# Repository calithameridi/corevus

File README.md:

# corevus

Copyright 2024 by meridi (myself), all rights reserved until I decide on a suitable license

Corevus-G v0.6 printer mainboards are available for evaluation and beta testing. Join the discord: 
`discord (dot) gg (slash) W 5 m a f w 2 k Y h`. **See the [Corevus-G v0.6 manual here](./docs/CvG-v0.6-beta/CvG-v0.6-manual.md)** for more information.

High performance, low-ish price control board for 3D printers. 

(For older hardware releases, also see the [CvG v0.4 manual](./docs/CvG-v0.4-beta/CvG-v0.4-hardware-overview.md))

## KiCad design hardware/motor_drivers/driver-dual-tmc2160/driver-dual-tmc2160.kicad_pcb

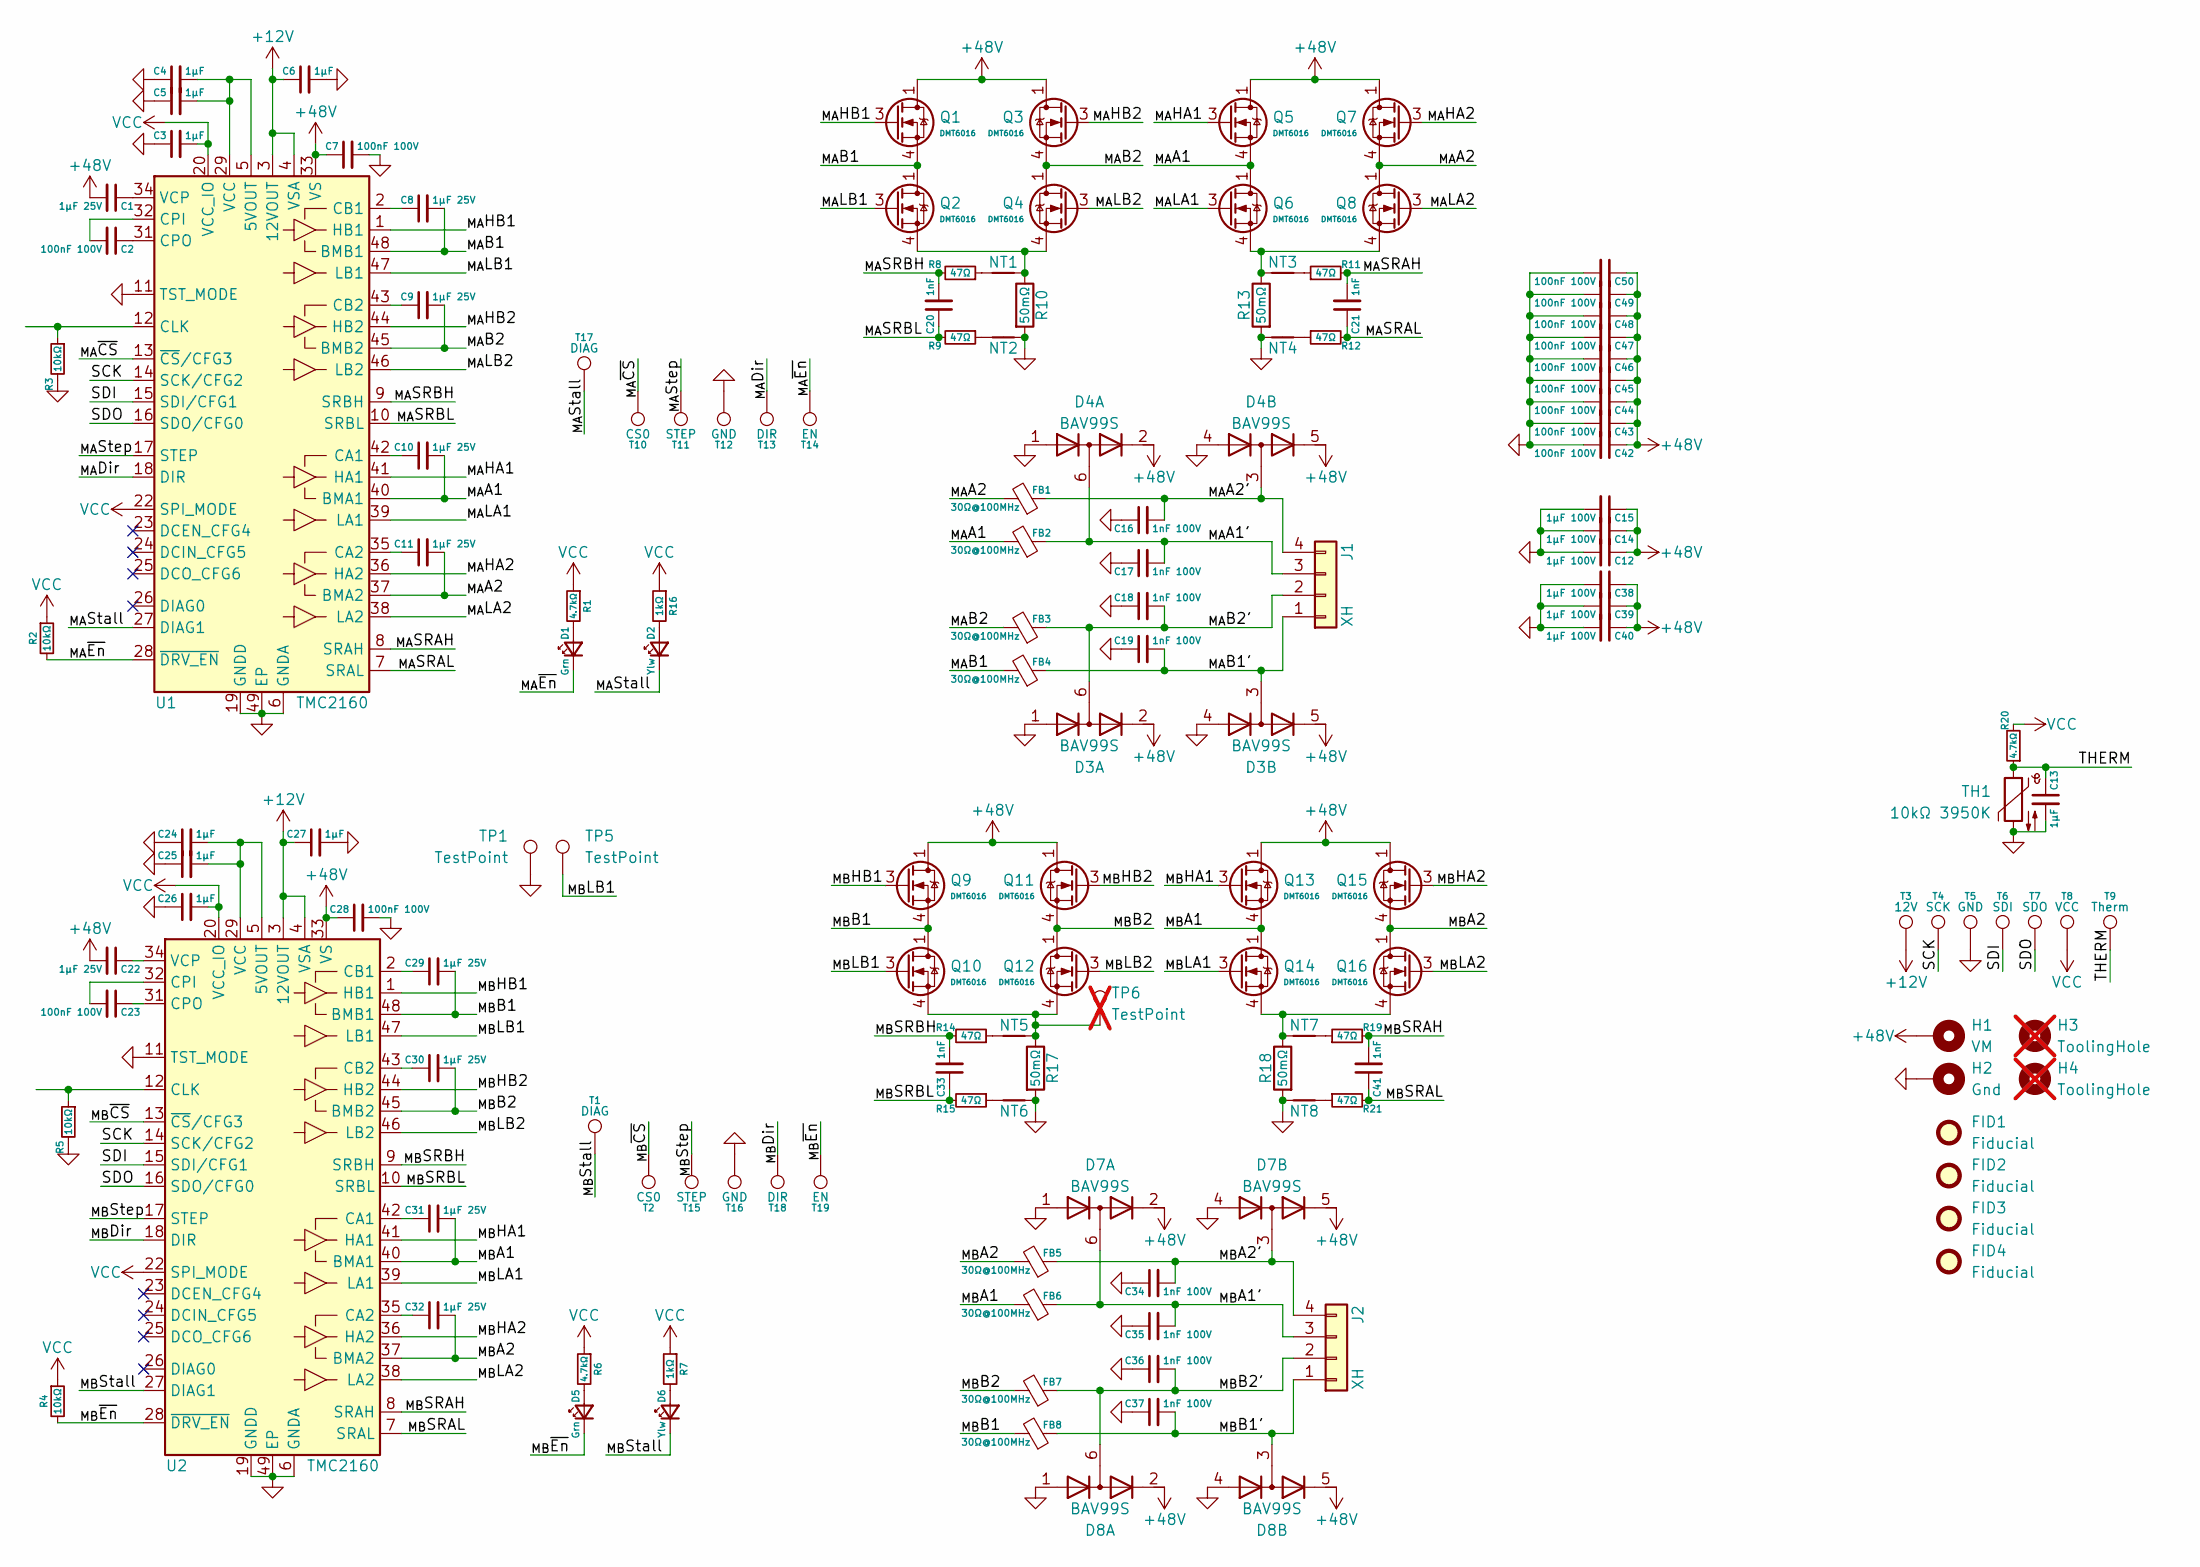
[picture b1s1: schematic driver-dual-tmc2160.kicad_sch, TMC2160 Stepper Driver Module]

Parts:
C1, C8, C9, C10, C11, C22, C29, C30, C31, C32: 1μF 25V; 0402C
C2, C7, C23, C28, C42, C43, C44, C45, C46, C47, C48, C49, C50: 100nF 100V; 0402C
C3, C5, C25, C26: 1µF; 0402C
C4, C6, C13, C24, C27: 1μF; 0402C
C12, C14, C15, C38, C39, C40: 1μF 100V; C_1206_3216Metric
C16, C17, C18, C19, C34, C35, C36, C37: 1nF 100V; 0402C
C20, C21, C33, C41: 1nF; 0402C
D1, D5: Grn; 0603LED
D2, D6: Ylw; 0603LED
D3, D4, D7, D8: BAV99S; SOT-363_SC-70-6
FB1, FB2, FB3, FB4, FB5, FB6, FB7, FB8: 30Ω@100MHz; R_1206_3216Metric
FID1, FID2, FID3, FID4: Fiducial; Fiducial_0.5mm_Mask1mm
H1: VM; MountingHole_M3_Driver
H2: Gnd; MountingHole_M3_Driver
H3, H4: ToolingHole; not fitted
J1, J2: XH; JST_XH_1x04
NT1, NT2, NT3, NT4, NT5, NT6, NT7, NT8: NetTie_2; NetTie-2_SMD_Pad0.15mm
Q1, Q2, Q3, Q4, Q5, Q6, Q7, Q8, Q9, Q10, Q11, Q12, Q13, Q14, Q15, Q16: DMT6016; DMT6016LFDF; LCSC Part C460205
R1, R6, R20: 4.7kΩ; 0402R
R2, R3, R4, R5: 10kΩ; 0402R
R7, R16: 1kΩ; 0402R
R8, R9, R11, R12, R14, R15, R19, R21: 47Ω; 0402R
R10, R13, R17, R18: 50mΩ; R_1206_3216Metric
T1, T17: DIAG; LGA_Land_2.5mm
T2, T10: CS0; LGA_Land_2.5mm
T3: 12V; LGA_Land_2.5mm
T4: SCK; LGA_Land_2.5mm
T5, T12, T16: GND; LGA_Land_2.5mm
T6: SDI; LGA_Land_2.5mm
T7: SDO; LGA_Land_2.5mm
T8: VCC; LGA_Land_2.5mm
T9: Therm; LGA_Land_2.5mm
T11, T15: STEP; LGA_Land_2.5mm
T13, T18: DIR; LGA_Land_2.5mm
T14, T19: EN; LGA_Land_2.5mm
TH1: 10kΩ 3950K; 0402R
TP1, TP5: TestPoint; TestPoint_Pad_D1.0mm
TP6: TestPoint; TestPoint_Pad_D1.0mm; not fitted
U1, U2: TMC2160; TMCx160

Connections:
+12V: C6.1, C27.1, T3.1, U1.3 (12VOUT), U1.4 (VSA), U2.3 (12VOUT), U2.4 (VSA)
+48V: C1.2, C7.1, C12.1, C14.1, C15.1, C22.2, C28.1, C38.1, C39.1, C40.1, C42.1, C43.1, C44.1, C45.1, C46.1, C47.1, C48.1, C49.1, C50.1, D3.2 (K2), D3.5 (K4), D4.2 (K2), D4.5 (K4), D7.2 (K2), D7.5 (K4), D8.2 (K2), D8.5 (K4), H1.1, Q1.1 (D), Q1.2 (D), Q1.5 (D), Q1.6 (D), Q1.8 (D), Q3.1 (D), Q3.2 (D), Q3.5 (D), Q3.6 (D), Q3.8 (D), Q5.1 (D), Q5.2 (D), Q5.5 (D), Q5.6 (D), Q5.8 (D), Q7.1 (D), Q7.2 (D), Q7.5 (D), Q7.6 (D), Q7.8 (D), Q9.1 (D), Q9.2 (D), Q9.5 (D), Q9.6 (D), Q9.8 (D), Q11.1 (D), Q11.2 (D), Q11.5 (D), Q11.6 (D), Q11.8 (D), Q13.1 (D), Q13.2 (D), Q13.5 (D), Q13.6 (D), Q13.8 (D), Q15.1 (D), Q15.2 (D), Q15.5 (D), Q15.6 (D), Q15.8 (D), U1.33 (VS), U2.33 (VS)
/SCK: T4.1, U1.14 (SCK/CFG2), U2.14 (SCK/CFG2)
/SDI: T6.1, U1.15 (SDI/CFG1), U2.15 (SDI/CFG1)
/SDO: T7.1, U1.16 (SDO/CFG0), U2.16 (SDO/CFG0)
/THERM: C13.1, R20.1, T9.1, TH1.1
/_{MA}A1: C10.2, FB2.2, Q5.4 (S), Q5.7 (S), Q6.1 (D), Q6.2 (D), Q6.5 (D), Q6.6 (D), Q6.8 (D), U1.40 (BMA1)
/_{MA}A1': C17.2, D4.6 (K3A4), FB2.1, J1.3
/_{MA}A2: C11.2, FB1.2, Q7.4 (S), Q7.7 (S), Q8.1 (D), Q8.2 (D), Q8.5 (D), Q8.6 (D), Q8.8 (D), U1.37 (BMA2)
/_{MA}A2': C16.2, D4.3 (K1A2), FB1.1, J1.4
/_{MA}B1: C8.2, FB4.2, Q1.4 (S), Q1.7 (S), Q2.1 (D), Q2.2 (D), Q2.5 (D), Q2.6 (D), Q2.8 (D), U1.48 (BMB1)
/_{MA}B1': C19.2, D3.3 (K1A2), FB4.1, J1.1
/_{MA}B2: C9.2, FB3.2, Q3.4 (S), Q3.7 (S), Q4.1 (D), Q4.2 (D), Q4.5 (D), Q4.6 (D), Q4.8 (D), U1.45 (BMB2)
/_{MA}B2': C18.2, D3.6 (K3A4), FB3.1, J1.2
/_{MA}Dir: T13.1, U1.18 (DIR)
/_{MA}HA1: Q5.3 (G), U1.41 (HA1)
/_{MA}HA2: Q7.3 (G), U1.36 (HA2)
/_{MA}HB1: Q1.3 (G), U1.1 (HB1)
/_{MA}HB2: Q3.3 (G), U1.44 (HB2)
/_{MA}LA1: Q6.3 (G), U1.39 (LA1)
/_{MA}LA2: Q8.3 (G), U1.38 (LA2)
/_{MA}LB1: Q2.3 (G), U1.47 (LB1)
/_{MA}LB2: Q4.3 (G), U1.46 (LB2)
/_{MA}SRAH: C21.2, R11.2, U1.8 (SRAH)
/_{MA}SRAL: C21.1, R12.2, U1.7 (SRAL)
/_{MA}SRBH: C20.2, R8.2, U1.9 (SRBH)
/_{MA}SRBL: C20.1, R9.2, U1.10 (SRBL)
/_{MA}Stall: D2.1 (K), T17.1, U1.27 (DIAG1)
/_{MA}Step: T11.1, U1.17 (STEP)
/_{MA}~CS: T10.1, U1.13 (~CS/CFG3)
/_{MA}~En: D1.1 (K), R2.2, T14.1, U1.28 (~DRV_EN)
/_{MB}A1: C31.2, FB6.2, Q13.4 (S), Q13.7 (S), Q14.1 (D), Q14.2 (D), Q14.5 (D), Q14.6 (D), Q14.8 (D), U2.40 (BMA1)
/_{MB}A1': C35.2, D7.6 (K3A4), FB6.1, J2.3
/_{MB}A2: C32.2, FB5.2, Q15.4 (S), Q15.7 (S), Q16.1 (D), Q16.2 (D), Q16.5 (D), Q16.6 (D), Q16.8 (D), U2.37 (BMA2)
/_{MB}A2': C34.2, D7.3 (K1A2), FB5.1, J2.4
/_{MB}B1: C29.2, FB8.2, Q9.4 (S), Q9.7 (S), Q10.1 (D), Q10.2 (D), Q10.5 (D), Q10.6 (D), Q10.8 (D), U2.48 (BMB1)
/_{MB}B1': C37.2, D8.3 (K1A2), FB8.1, J2.1
/_{MB}B2: C30.2, FB7.2, Q11.4 (S), Q11.7 (S), Q12.1 (D), Q12.2 (D), Q12.5 (D), Q12.6 (D), Q12.8 (D), U2.45 (BMB2)
/_{MB}B2': C36.2, D8.6 (K3A4), FB7.1, J2.2
/_{MB}Dir: T18.1, U2.18 (DIR)
/_{MB}HA1: Q13.3 (G), U2.41 (HA1)
/_{MB}HA2: Q15.3 (G), U2.36 (HA2)
/_{MB}HB1: Q9.3 (G), U2.1 (HB1)
/_{MB}HB2: Q11.3 (G), U2.44 (HB2)
/_{MB}LA1: Q14.3 (G), U2.39 (LA1)
/_{MB}LA2: Q16.3 (G), U2.38 (LA2)
/_{MB}LB1: Q10.3 (G), TP5.1, U2.47 (LB1)
/_{MB}LB2: Q12.3 (G), U2.46 (LB2)
/_{MB}SRAH: C41.2, R19.2, U2.8 (SRAH)
/_{MB}SRAL: C41.1, R21.2, U2.7 (SRAL)
/_{MB}SRBH: C33.2, R14.2, U2.9 (SRBH)
/_{MB}SRBL: C33.1, R15.2, U2.10 (SRBL)
/_{MB}Stall: D6.1 (K), T1.1, U2.27 (DIAG1)
/_{MB}Step: T15.1, U2.17 (STEP)
/_{MB}~CS: T2.1, U2.13 (~CS/CFG3)
/_{MB}~En: D5.1 (K), R4.2, T19.1, U2.28 (~DRV_EN)
GND: C3.1, C4.1, C5.1, C6.2, C7.2, C12.2, C13.2, C14.2, C15.2, C16.1, C17.1, C18.1, C19.1, C24.1, C25.1, C26.1, C27.2, C28.2, C34.1, C35.1, C36.1, C37.1, C38.2, C39.2, C40.2, C42.2, C43.2, C44.2, C45.2, C46.2, C47.2, C48.2, C49.2, C50.2, D3.1 (A1), D3.4 (A3), D4.1 (A1), D4.4 (A3), D7.1 (A1), D7.4 (A3), D8.1 (A1), D8.4 (A3), H2.1, NT2.2, NT4.1, NT6.2, NT8.1, R3.2, R5.2, R10.2, R13.2, R17.2, R18.2, T5.1, T12.1, T16.1, TH1.2, TP1.1, U1.6 (GNDA), U1.11 (TST_MODE), U1.19 (GNDD), U1.30 (GNDD), U1.49 (EP), U2.6 (GNDA), U2.11 (TST_MODE), U2.19 (GNDD), U2.30 (GNDD), U2.49 (EP)
unnamed: D1.2 (A), R1.2
unnamed: D2.2 (A), R16.2
unnamed: D5.2 (A), R6.2
unnamed: D6.2 (A), R7.2
unnamed: NT1.1, R8.1
unnamed: NT1.2, Q2.4 (S), Q2.7 (S), Q4.4 (S), Q4.7 (S), R10.1
unnamed: NT2.1, R9.1
unnamed: NT3.1, Q6.4 (S), Q6.7 (S), Q8.4 (S), Q8.7 (S), R13.1
unnamed: NT3.2, R11.1
unnamed: NT4.2, R12.1
unnamed: NT5.1, R14.1
unnamed: NT5.2, Q10.4 (S), Q10.7 (S), Q12.4 (S), Q12.7 (S), R17.1, TP6.1
unnamed: NT6.1, R15.1
unnamed: NT7.1, Q14.4 (S), Q14.7 (S), Q16.4 (S), Q16.7 (S), R18.1
unnamed: NT7.2, R19.1
unnamed: NT8.2, R21.1
unnamed: C4.2, C5.2, U1.5 (5VOUT), U1.29 (VCC)
unnamed: C10.1, U1.42 (CA1)
unnamed: C11.1, U1.35 (CA2)
unnamed: C8.1, U1.2 (CB1)
unnamed: C9.1, U1.43 (CB2)
unnamed: R3.1, U1.12 (CLK)
unnamed: C2.2, U1.32 (CPI)
unnamed: C2.1, U1.31 (CPO)
unnamed: C1.1, U1.34 (VCP)
unnamed: C24.2, C25.2, U2.5 (5VOUT), U2.29 (VCC)
unnamed: C31.1, U2.42 (CA1)
unnamed: C32.1, U2.35 (CA2)
unnamed: C29.1, U2.2 (CB1)
unnamed: C30.1, U2.43 (CB2)
unnamed: R5.1, U2.12 (CLK)
unnamed: C23.2, U2.32 (CPI)
unnamed: C23.1, U2.31 (CPO)
unnamed: C22.1, U2.34 (VCP)
VCC: C3.2, C26.2, R1.1, R2.1, R4.1, R6.1, R7.1, R16.1, R20.2, T8.1, U1.20 (VCC_IO), U1.21 (VCC_IO), U1.22 (SPI_MODE), U2.20 (VCC_IO), U2.21 (VCC_IO), U2.22 (SPI_MODE)

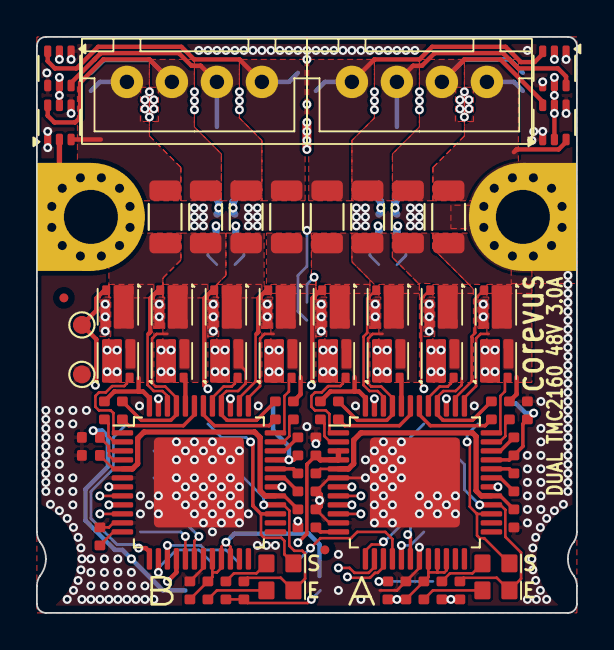
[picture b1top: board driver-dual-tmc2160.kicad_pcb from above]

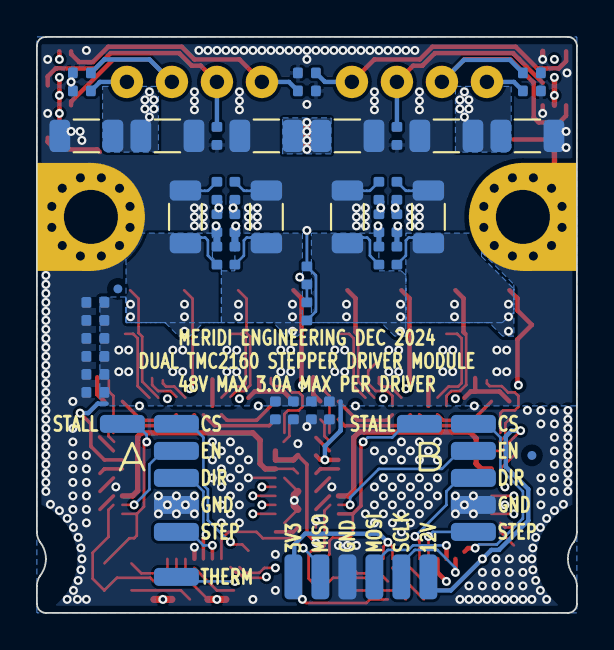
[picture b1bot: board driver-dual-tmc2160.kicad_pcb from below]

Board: 4 copper layers, 30.0 x 32.0 mm, 143 parts (71 on the bottom side), 92 nets.

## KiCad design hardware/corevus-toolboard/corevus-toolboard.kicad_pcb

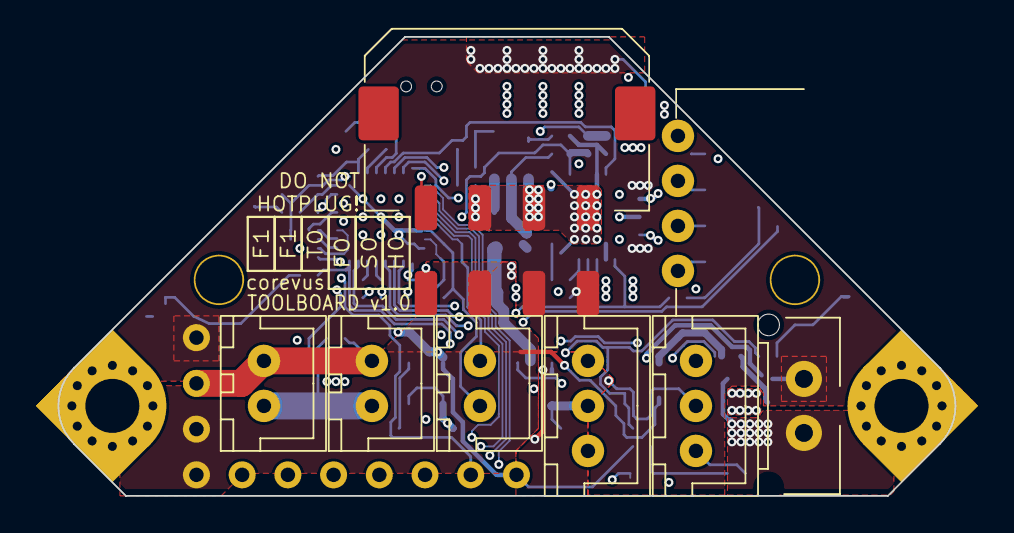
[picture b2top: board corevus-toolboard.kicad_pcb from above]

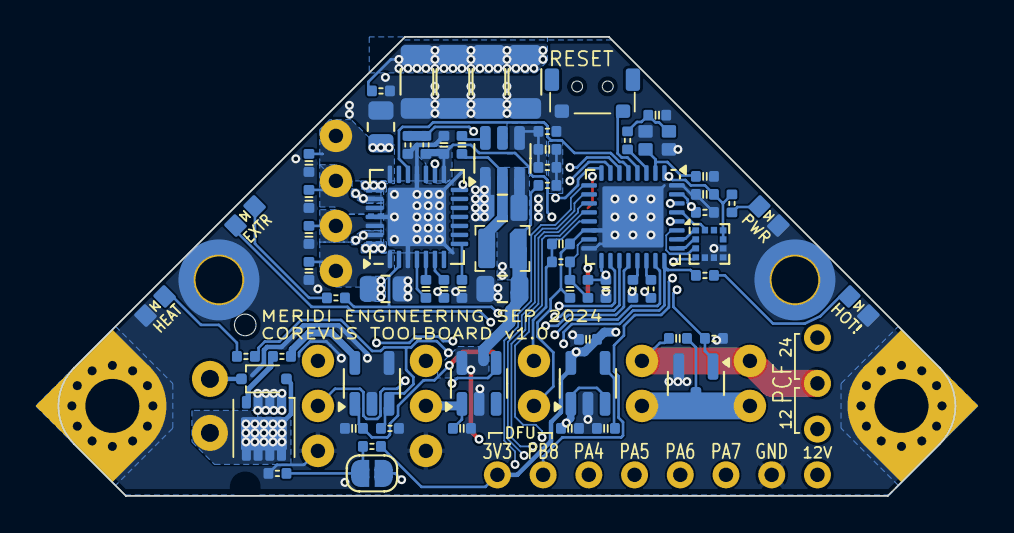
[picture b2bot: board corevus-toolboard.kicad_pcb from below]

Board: 4 copper layers, 49.8 x 25.5 mm, 84 parts (72 on the bottom side), 62 nets.

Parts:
C1, C4, C5, C6, C11, C12, C13, C26, C34: 1µF; 0402C
C2, C3: 10pF; 0402C
C7: 100nF; 0402C
C8: 100nF 16V; 0402C
C9: 22nF 50V; 0402C
C14, C15, C16, C17: 10µF 50V; C_1206_3216Metric
C18, C19, C20, C21: 470pF; 0402C
C23: 100nF 50V; 0402C
C28: 68pF; 0402C
C29: 100nF 25V; 0402C
C31: 10nF; 0402C
C32: 10µF 25V; C_0805_2012Metric
C33: 10µF; C_0805_2012Metric
D1: 4148; D_SOD-323
D2: Red; 0603LED
D3: Grn; 0603LED
D4: Wht; 0603LED
D5: Ylw; 0603LED
FB1: GZ1005; 0402
H1, H2: M3 Hole; MountingHole_M3_Driver_Corner
H3, H4: M2 Standoff; Sinhoo_TH162010
J1: MF3 1x2P; Molex_Micro-Fit-3.0_436500215
J2, J9: XH 1x3P; JST_XH_1x03
J3: MX3.0 2x4P; XKB_X3025WRS-2x04E
J4: XH 1x4P; JST_XH_1x04-Side
J5, J6, J7: XH 1x2P; JST_XH_1x02
J8: 1x8P; PinHeader_1x08_P2.54mm_Vertical
J10: 1x3P; PinHeader_1x03_P2.54mm_Vertical
JP1: Jumper_2_Small_Open; SolderJumper-2_P1.3mm_Open_RoundedPad1.0x1.5mm
L1: 10µH; L_Changjiang_FTC2520
NT1: NetTie_2; NetTie-2_SMD_Pad0.1mm
Q2: NMOS; MOSFET_DFN8
Q4: AO3400; SOT-23
R1, R7, R16: 4.7kΩ; 0402R
R2: 100kΩ; 0402R
R3, R4: 33Ω; 0402R
R5, R6: 100mΩ; R_0805_2012Metric
R8, R13, R17, R21: 2.2kΩ; 0402R
R9: 0Ω; 0402R
R10: 20kΩ; 0402R
R11: 150kΩ; 0402R
R12: 1kΩ; 0402R
R14, R19: 10kΩ; 0402R
R15: 51Ω; 0402R
R20: 510kΩ; 0402R
SW1: Reset; ShouHan_TS24CA
TH1, TH2: 10kΩ 3950K; 0402R
U1: LIS2DE12; LGA-12_2x2mm_P0.5mm
U2: TPS54302; SOT-23-6
U3: STM32G431KBU3; QFN-32-1EP_5x5mm_P0.5mm_EP3.45x3.45mm
U4: TMC2209-LA; TQFN-28-1EP_5x5mm_P0.5mm_EP3.25x3.25mm_ThermalVias
U6: SPX3819M5-L-3-3; SOT-23-5
U7: TPS2069CDBV; SOT-23-5
U8: UCC27517; SOT-23-5
Y1: XRCGB25; Crystal_SMD_2016-4Pin_2.0x1.6mm

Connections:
+3.3V: C5.1, C11.1, C12.1, C34.2, D3.2 (A), FB1.2, J8.8, R7.2, R16.2, R17.2, U1.9 (Vdd), U1.10 (Vdd_IO), U3.1 (VDD), U3.17 (VDD), U4.15 (VCC_IO), U6.5 (OUT)
+5V: C1.2, C33.1, J9.2, L1.2, R15.1, U6.1 (IN), U6.3 (EN), U7.5 (IN)
+12V: C29.1, C32.1, J3.6, J8.1, J10.3, U2.3 (VIN), U8.1 (VDD)
+24V: C8.2, C14.1, C15.1, C16.1, C17.1, D1.1 (K), J1.2, J3.7, J3.8, J10.1, R20.1, U4.22 (VS), U4.28 (VS)
/A1: C19.1, J4.3, U4.24 (OA1)
/A2: C18.1, J4.4, U4.21 (OA2)
/ACCEL_CS: U1.2 (~CS), U3.25 (PA15)
/ACCEL_INT1: U1.12 (INT1), U3.29 (PB6)
/B1: C21.1, J4.1, U4.1 (OB2)
/B2: C20.1, J4.2, U4.26 (OB1)
/BOOT0: J8.7, R2.2, U3.31 (PB8)
/D+: J3.5, R3.2
/D+': R3.1, U3.22 (USB_DP)
/D-: J3.1, R4.2
/D-': R4.1, U3.21 (USB_DM)
/Dir: U3.5 (PA0), U4.19 (DIR)
/F0: R8.2, U3.24 (PA14), U7.4 (EN)
/F0_FG: J2.3, U3.19 (PA9)
/F1: Q4.1 (G), R14.1, U3.30 (PB7)
/H0: R1.2, R19.2, U3.23 (PA13), U8.3 (IN+)
/H0_Gate: R9.2, U8.5 (OUT)
/PA4: J8.6, JP1.2 (B), U3.9 (ADC2_IN17)
/PA5: J8.5, U3.10 (ADC2_IN13)
/PA6: J8.4, U3.11 (ADC2_IN3)
/PA7: J8.3, U3.12 (ADC2_IN4)
/PCF_V+: C23.1, J6.2, J7.2, J10.2
/S0: J9.3, U3.20 (PA10)
/SPI1_MISO: U1.3 (SA0/SDO), U3.27 (SPI1_MISO)
/SPI1_MOSI: U1.4 (SDA/SDI), U3.28 (SPI1_MOSI)
/SPI1_SCK: U1.1 (SCL/SPC), U3.26 (SPI1_SCK)
/Step: U3.7 (PA2), U4.16 (STEP)
/T0: C26.1, J5.2, R13.1, U3.13 (PB0)
/UART: U3.8 (PA3), U4.14 (PDN/UART)
/_{FET}Therm: JP1.1 (A), R7.1, TH2.1
/_{Motor}Therm: R16.1, TH1.1, U3.6 (ADC1_IN2)
/~En: R21.2, U3.18 (PA8), U4.2 (~EN)
/~Reset: SW1.1, U3.4 (PG10)
GND: C1.1, C2.2, C3.2, C4.2, C5.2, C6.2, C11.2, C12.2, C14.2, C15.2, C16.2, C17.2, C18.2, C19.2, C20.2, C21.2, C29.2, C31.1, C32.2, C33.2, C34.1, D2.1 (K), D4.1 (K), D5.1 (K), H1.1, H2.1, H3.1, H4.1, J2.1, J3.2, J3.3, J3.4, J8.2, J9.1, NT1.1, Q2.1 (S), Q2.2 (S), Q2.3 (S), Q4.2 (S), R2.1, R5.1, R6.1, R10.2, R14.2, R19.1, R20.2, SW1.2, TH1.2, TH2.2, U1.5 (RES), U1.6 (GND), U1.7 (GND), U1.8 (GND), U2.1 (GND), U3.16 (VSS), U3.32 (VSS), U3.33 (VSS), U4.3 (GND), U4.18 (Gnd), U4.25 (NC), U4.29 (Pad), U6.2 (GND), U7.2 (GND), U8.2 (GND), U8.4 (IN-), Y1.2, Y1.4
unnamed: C3.1, R12.1, Y1.1
unnamed: C28.1, R11.1, R15.2
unnamed: D1.2 (A), J1.1, Q2.5 (D), Q2.6 (D), Q2.7 (D), Q2.8 (D)
unnamed: D2.2 (A), R1.1
unnamed: D3.1 (K), R21.1
unnamed: D4.2 (A), R17.1
unnamed: D5.2 (A), R8.1
unnamed: C6.1, J2.2, U7.1 (OUT)
unnamed: C23.2, J6.1, J7.1, Q4.3 (D)
unnamed: Q2.4 (G), R9.1
unnamed: C7.1, U2.6 (BOOT)
unnamed: C28.2, R10.1, R11.2, U2.4 (FB)
unnamed: C7.2, L1.1, U2.2 (SW)
unnamed: C2.1, U3.2 (RCC_OSC_IN), Y1.3
unnamed: R12.2, U3.3 (RCC_OSC_OUT)
unnamed: C4.1, U4.8 (5VOUT)
unnamed: R5.2, U4.23 (BRA)
unnamed: R6.2, U4.27 (BRB)
unnamed: C9.2, U4.5 (CPI)
unnamed: C9.1, U4.4 (CPO)
unnamed: C8.1, U4.6 (VCP)
unnamed: C31.2, U6.4 (BP)
VDDA: C13.2, FB1.1, R13.2, U3.15 (VDDA)
VSSA: C13.1, C26.2, J5.1, NT1.2, U3.14 (VSSA)

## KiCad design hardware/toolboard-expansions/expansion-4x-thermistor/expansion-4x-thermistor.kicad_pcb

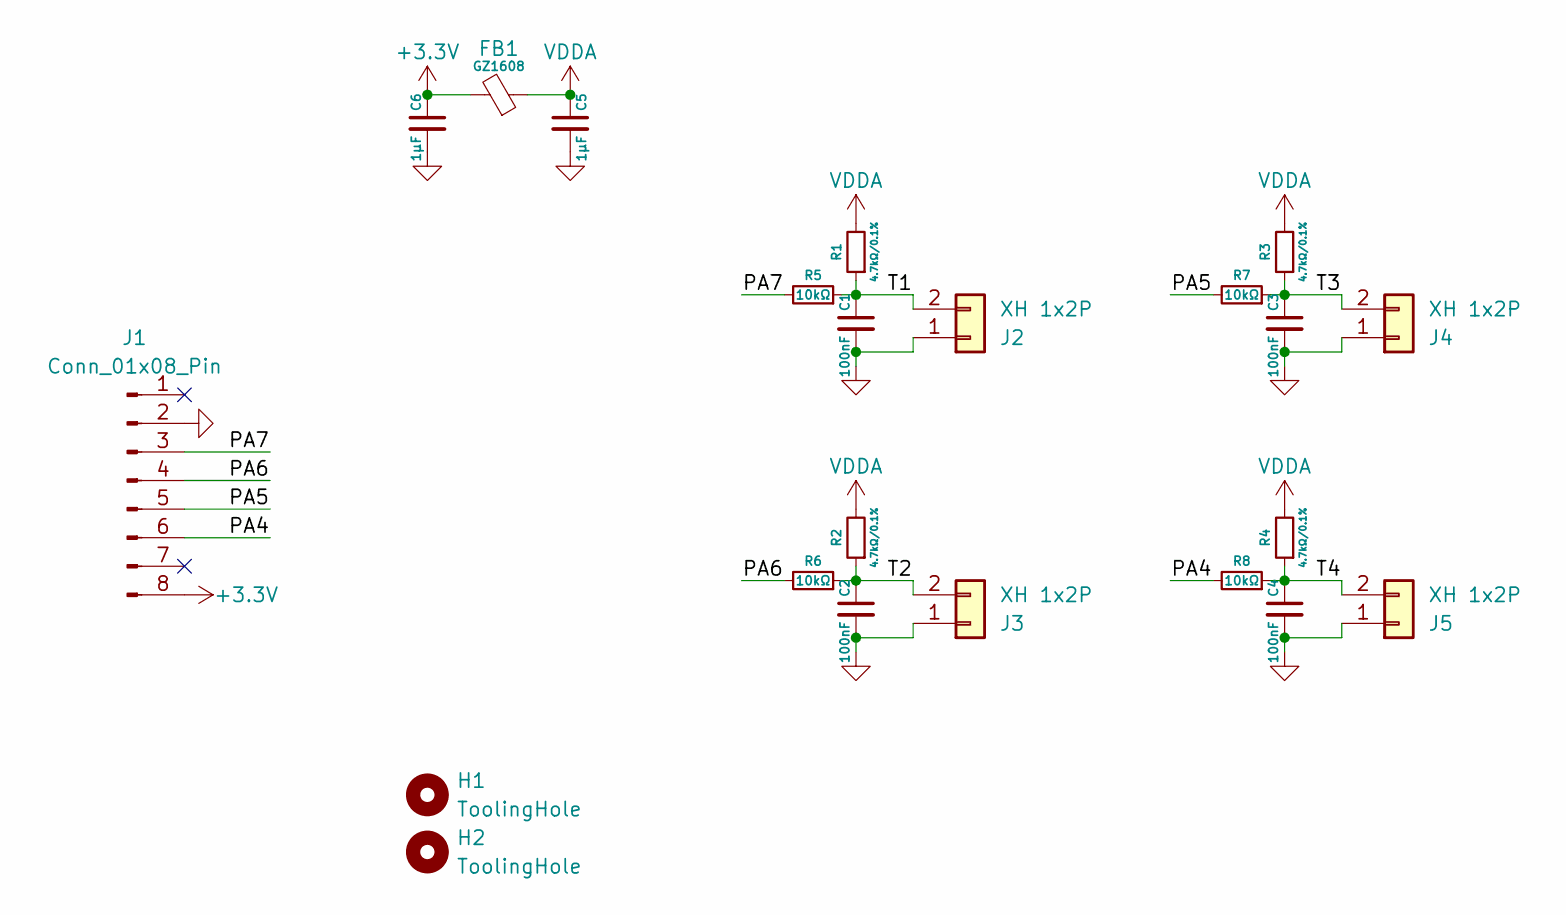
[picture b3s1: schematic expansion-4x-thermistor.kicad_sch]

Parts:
C1, C2, C3, C4: 100nF; 0402C
C5, C6: 1µF; 0402C
FB1: GZ1608; 0603
H1, H2: ToolingHole
J1: Conn_01x08_Pin; PinHeader_1x08_P2.54mm_Vertical
J2, J3, J4, J5: XH 1x2P; JST_XH_1x02-Side
R1, R2, R3, R4: 4.7kΩ/0.1%; 0402R
R5, R6, R7, R8: 10kΩ; 0402R

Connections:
+3.3V: C6.1, FB1.2, J1.8
/PA4: J1.6, R8.2
/PA5: J1.5, R7.2
/PA6: J1.4, R6.2
/PA7: J1.3, R5.2
/T1: C1.1, J2.2, R1.1, R5.1
/T2: C2.1, J3.2, R2.1, R6.1
/T3: C3.1, J4.2, R3.1, R7.1
/T4: C4.1, J5.2, R4.1, R8.1
GND: C1.2, C2.2, C3.2, C4.2, C5.2, C6.2, J1.2, J2.1, J3.1, J4.1, J5.1
VDDA: C5.1, FB1.1, R1.2, R2.2, R3.2, R4.2

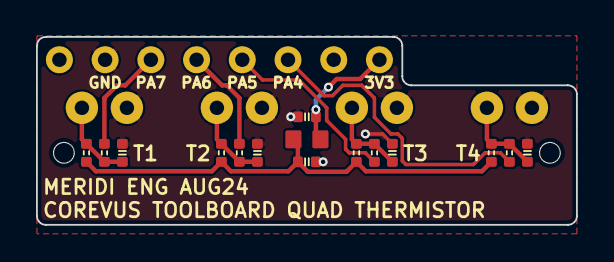
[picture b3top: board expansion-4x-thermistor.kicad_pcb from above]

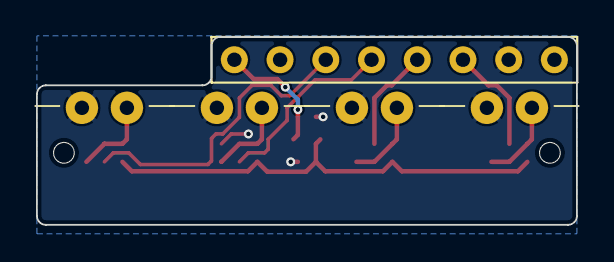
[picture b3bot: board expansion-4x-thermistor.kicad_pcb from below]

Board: 2 copper layers, 30.0 x 10.4 mm, 22 parts (5 on the bottom side), 11 nets.

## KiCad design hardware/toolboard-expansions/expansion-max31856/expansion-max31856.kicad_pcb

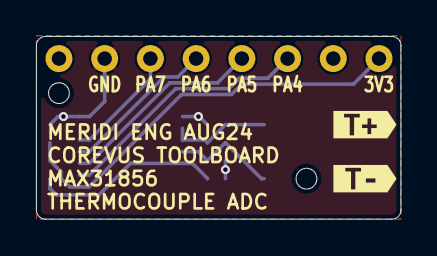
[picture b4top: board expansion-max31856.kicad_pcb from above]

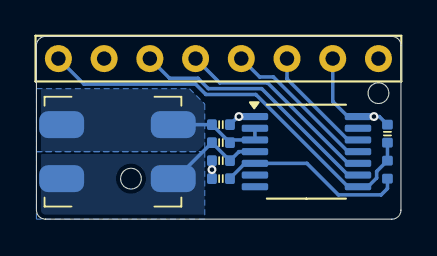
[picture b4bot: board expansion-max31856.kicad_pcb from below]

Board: 2 copper layers, 20.2 x 10.2 mm, 13 parts (9 on the bottom side), 9 nets.

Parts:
C1, C2, C5: 100nF; 0402C
C3, C4: 10nF; 0402C
H1, H2: ToolingHole
J1: Conn_01x08_Socket; PinHeader_1x08_P2.54mm_Vertical
J2: WAGO 1x2P; WAGO_2059-302
R1: 0Ω; 0402
U1: MAX31856; TSSOP-14_4.4x5mm_P0.65mm
kibuzzard-66C1A6C4: G***; kibuzzard-66C1A6C4
kibuzzard-66C1A6D0: G***; kibuzzard-66C1A6D0

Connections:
+3.3V: C1.1, J1.8, R1.1, U1.8 (DVDD)
/PA4: J1.6, U1.9 (~CS)
/PA5: J1.5, U1.10 (SCK)
/PA6: J1.4, U1.11 (SDO)
/PA7: J1.3, U1.12 (SDI)
/T+: C3.2, C5.1, J2.2, U1.4 (T+)
/T-: C4.2, C5.2, J2.1, U1.2 (BIAS), U1.3 (T-)
GND: C1.2, C2.2, C3.1, C4.1, J1.2, U1.1 (AGND), U1.14 (DGND)
VDDA: C2.1, R1.2, U1.5 (AVDD)

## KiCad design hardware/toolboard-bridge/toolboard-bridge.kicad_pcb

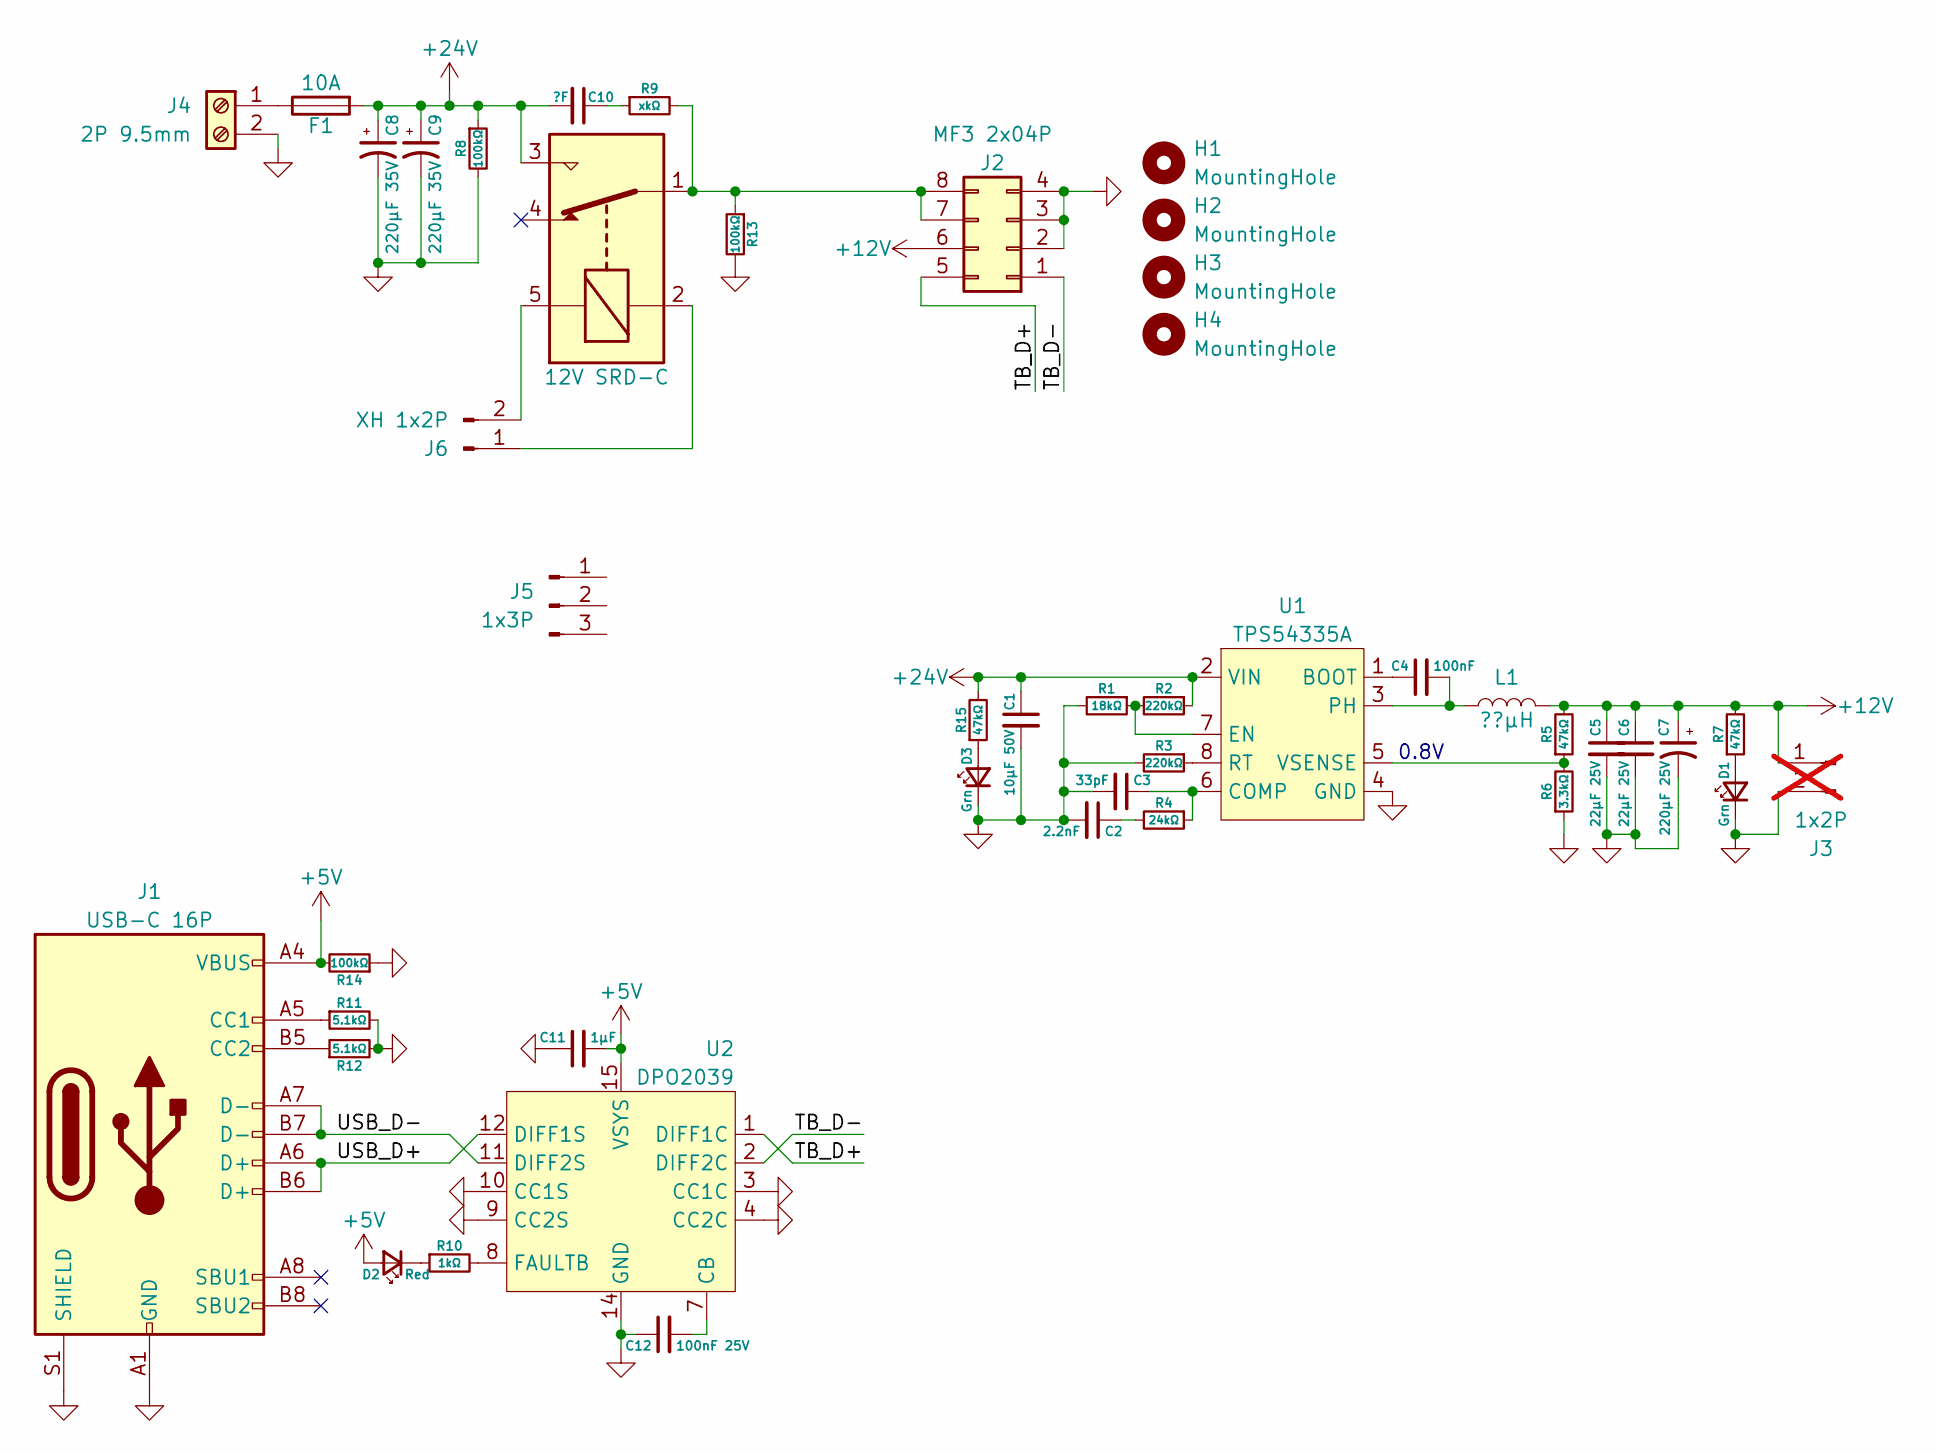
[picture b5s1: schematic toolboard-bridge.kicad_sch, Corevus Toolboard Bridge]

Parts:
C1: 10μF 50V; C_1206_3216Metric
C2: 2.2nF; 0402C
C3: 33pF; 0402C
C4: 100nF; 0402C
C5, C6: 22μF 25V; C_1206_3216Metric
C7: 220μF 25V; CP_Radial_D8.0mm_P3.50mm
C8, C9: 220μF 35V; CP_Radial_D8.0mm_P3.50mm
C10: ?F; C_1206_3216Metric
C11: 1μF; 0402C
C12: 100nF 25V; 0402C
D1, D3: Grn; 0603LED
D2: Red; 0603LED
F1: 10A; XF-506P
H1, H2, H3, H4: MountingHole; MountingHole_3.2mm_M3_DIN965
J1: USB-C 16P; USB_Type-C_16p
J2: MF3 2x04P; Molex_Micro-Fit-3.0_430450813
J3: 1x2P; PinHeader_1x02_P2.54mm_Vertical; not fitted
J4: 2P 9.5mm; Kefa_KF8500-8.5-2P
J5: 1x3P; PinHeader_1x03_P2.54mm_Vertical
J6: XH 1x2P; JST_XH_1x02
K1: 12V SRD-C; Relay_SPDT_SANYOU_SRD_Series_Form_C
L1: ??μH; L_Changjiang_FXL0640
R1: 18kΩ; 0402R
R2, R3: 220kΩ; 0402R
R4: 24kΩ; 0402R
R5: 47kΩ; 0603R
R6: 3.3kΩ; 0603R
R7, R15: 47kΩ; 0402R
R8, R13, R14: 100kΩ; 0402R
R9: xkΩ; 0402R
R10: 1kΩ; 0402R
R11, R12: 5.1kΩ; 0402R
U1: TPS54335A; SOIC-8-1EP_3.9x4.9mm_P1.27mm_EP2.95x4.9mm_Mask2.71x3.4mm_Th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
U2: DPO2039; VQFN-16-1EP_3x3mm_P0.5mm_EP1.6x1.6mm

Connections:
+5V: C11.2, D2.2 (A), J1.A4 (VBUS), J1.A9 (VBUS), J1.B4 (VBUS), J1.B9 (VBUS), R14.2, U2.15 (VSYS)
+12V: C5.1, C6.1, C7.1, J2.6, J3.1, L1.2, R5.2, R7.2
+24V: C1.1, C8.1, C9.1, C10.2, F1.2, K1.3, R2.1, R8.1, R15.2, U1.2 (VIN)
/TB_D+: J2.5, U2.1 (DIFF1C)
/TB_D-: J2.1, U2.2 (DIFF2C)
/USB_D+: J1.A6 (D+), J1.B6 (D+), U2.12 (DIFF1S)
/USB_D-: J1.A7 (D-), J1.B7 (D-), U2.11 (DIFF2S)
GND: C1.2, C2.2, C3.2, C5.2, C6.2, C7.2, C8.2, C9.2, C11.1, C12.1, D1.1 (K), D3.1 (K), J1.A1 (GND), J1.A12 (GND), J1.B1 (GND), J1.B12 (GND), J1.S1 (SHIELD), J2.2, J2.3, J2.4, J3.2, J4.2, R1.2, R3.2, R6.1, R8.2, R11.2, R12.2, R13.2, R14.1, U1.4 (GND), U1.9 (GND), U2.3 (CC1C), U2.4 (CC2C), U2.5 (NC), U2.6 (NC), U2.9 (CC2S), U2.10 (CC1S), U2.13 (NC), U2.14 (GND), U2.16 (NC), U2.17 (GND)
unnamed: C2.1, R4.2
unnamed: C10.1, R9.1
unnamed: D1.2 (A), R7.1
unnamed: D2.1 (K), R10.1
unnamed: D3.2 (A), R15.1
unnamed: J1.A5 (CC1), R11.1
unnamed: J1.B5 (CC2), R12.1
unnamed: J2.7, J2.8, K1.1, R9.2, R13.1
unnamed: F1.1, J4.1
unnamed: J6.1, K1.2
unnamed: J6.2, K1.5
unnamed: C4.1, U1.1 (BOOT)
unnamed: C3.1, R4.1, U1.6 (COMP)
unnamed: R1.1, R2.2, U1.7 (EN)
unnamed: C4.2, L1.1, U1.3 (PH)
unnamed: R3.1, U1.8 (RT)
unnamed: R5.1, R6.2, U1.5 (VSENSE)
unnamed: C12.2, U2.7 (CB)
unnamed: R10.2, U2.8 (FAULTB)

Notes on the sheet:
0.8V

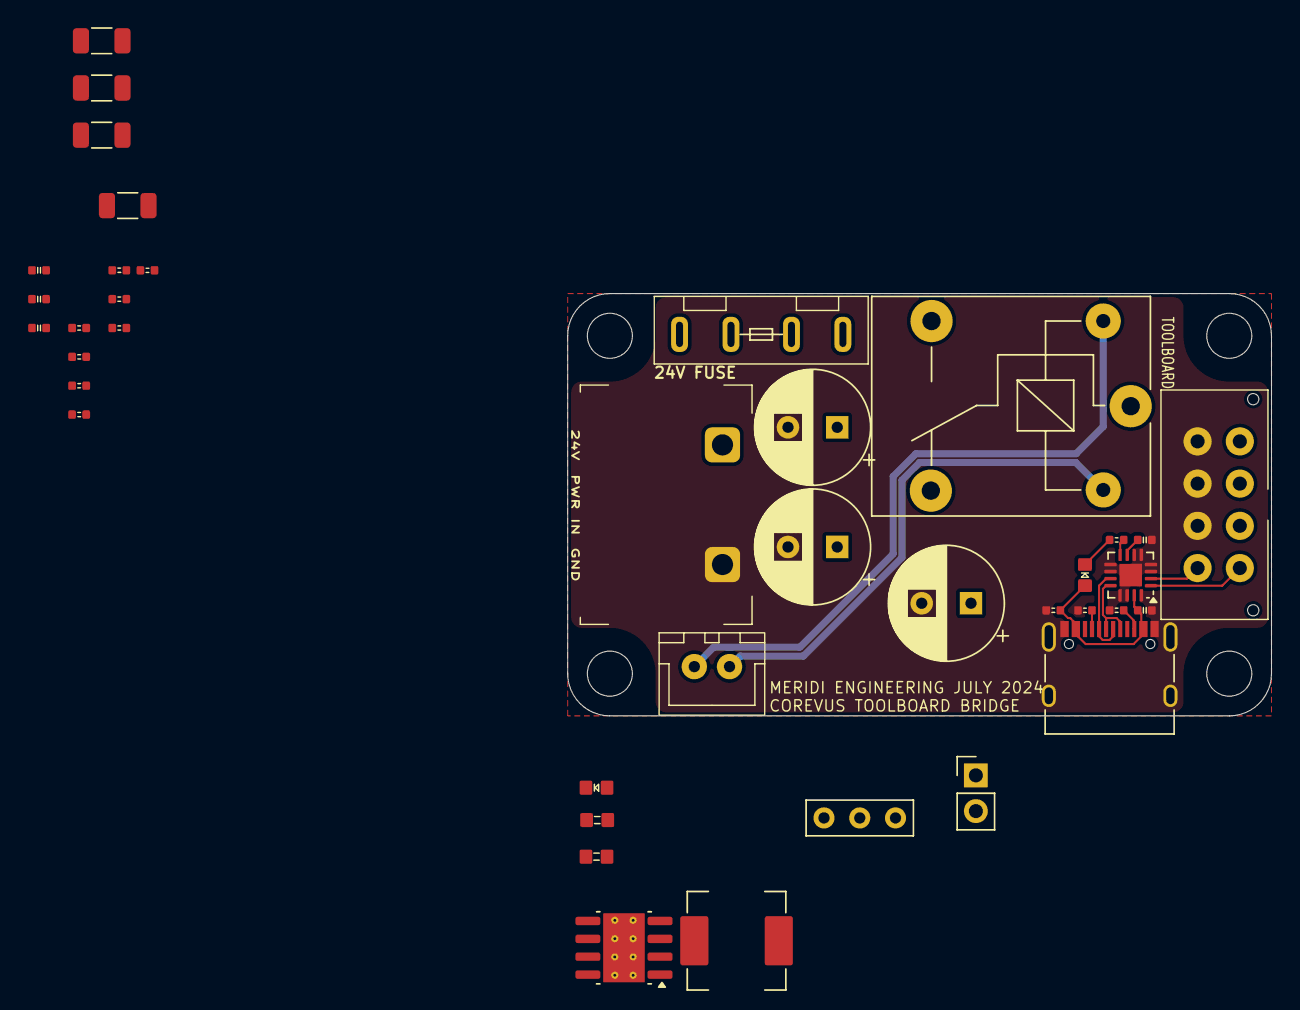
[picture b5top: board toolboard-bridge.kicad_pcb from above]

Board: 2 copper layers, 50.0 x 30.0 mm, 43 parts (0 on the bottom side), 26 nets.
